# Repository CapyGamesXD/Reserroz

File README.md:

# Reserroz

This is a less expensive alternative to the official Flipper Zero Wi-Fi Devboard. 

It is capable of running GhostESP and Wi-Fi Marauder*

The total cost for 2 units (shipping included) came out to <£30 each from JLCPCB - £5 less than the devboard. If they were manufactured manually, they would be significantly cheaper than the official version. It features an ESP32 S3 Mini 1 (double the cores than the official one, with Bluetooth!) as the main microcontroller chip. 

*As of now, neither has been tested as the device has not yet been manufactured.

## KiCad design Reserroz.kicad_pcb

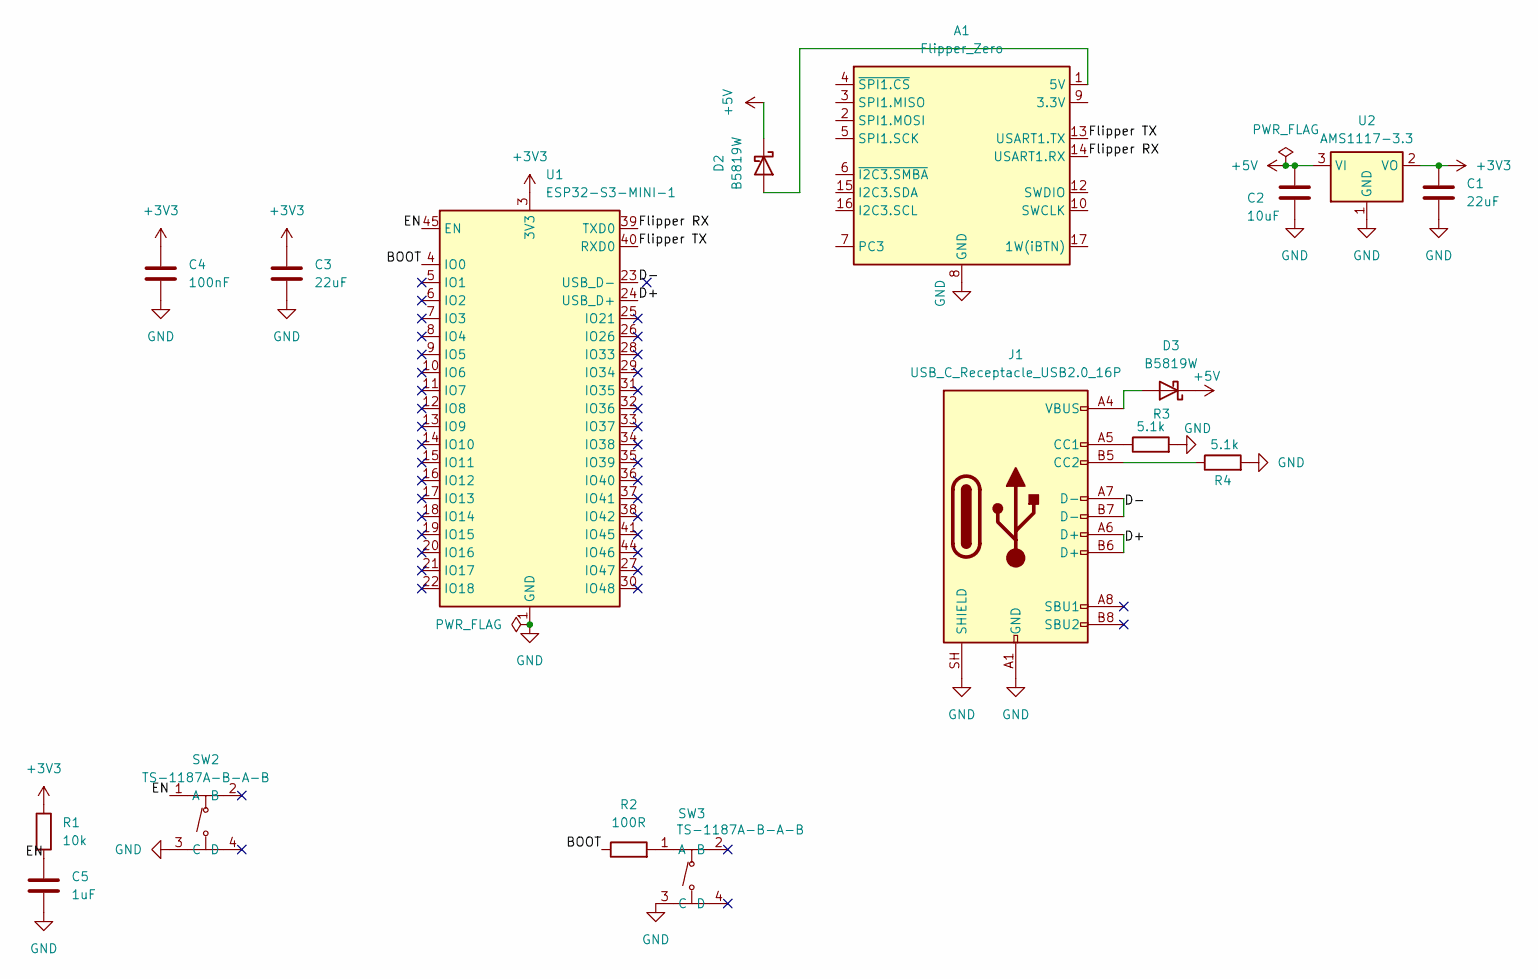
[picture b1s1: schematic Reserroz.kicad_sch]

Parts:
A1: Flipper_Zero; Flipper_Zero_Angled
C1, C3: 22uF; C_1210_3225Metric; LCSC C16196568
C2: 10uF; C_1210_3225Metric; LCSC C55072786
C4: 100nF; C_0603_1608Metric; LCSC C14663
C5: 1uF; C_0603_1608Metric; LCSC C14663
D2, D3: B5819W; D_SOD-123; LCSC C8598
J1: USB_C_Receptacle_USB2.0_16P; USB_C_Receptacle_GCT_USB4105-xx-A_16P_TopMnt_Horizontal
R1: 10k; R_0805_2012Metric
R2: 100R; R_0805_2012Metric; LCSC C2907218
R3, R4: 5.1k; R_0805_2012Metric
SW2, SW3: TS-1187A-B-A-B; SW-SMD_4P-L5.1-W5.1-P3.70-LS6.5-TL_H1.5; MPN TS-1187A-B-A-B; LCSC Part C318884
U1: ESP32-S3-MINI-1; ESP32-S2-MINI-1
U2: AMS1117-3.3; SOT-223-3_TabPin2

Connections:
+3V3: C1.1, C3.1, C4.1, R1.1, U1.3 (3V3), U2.2 (VO); also elsewhere on the board
+5V: C2.1, D2.1 (K), D3.1 (K), U2.3 (VI)
/BOOT: R2.1, U1.4 (IO0)
/D+: J1.A6 (D+), J1.B6 (D+), U1.24 (USB_D+)
/D-: J1.A7 (D-), J1.B7 (D-), U1.23 (USB_D-)
/EN: C5.1, R1.2, SW2.1 (A), U1.45 (EN)
/F5V: A1.1 (5V), D2.2 (A); also elsewhere on the board
/FSCL: A1.16 (I2C3.SCL); also elsewhere on the board
/FSDA: A1.15 (I2C3.SDA); also elsewhere on the board
/Flipper 3V3: A1.9 (3.3V); also elsewhere on the board
/Flipper RX: A1.14 (USART1.RX), U1.39 (TXD0)
/Flipper TX: A1.13 (USART1.TX), U1.40 (RXD0)
GND: A1.8 (GND), A1.11 (GND), A1.18 (GND), C1.2, C2.2, C3.2, C4.2, C5.2, J1.A1 (GND), J1.A12 (GND), J1.B1 (GND), J1.B12 (GND), J1.SH (SHIELD), R3.2, R4.2, SW2.3 (C), SW3.3 (C), U1.1 (GND), U1.2 (GND), U1.42 (GND), U1.43 (GND), U1.46 (GND), U1.47 (GND), U1.48 (GND), U1.49 (GND), U1.50 (GND), U1.51 (GND), U1.52 (GND), U1.53 (GND), U1.54 (GND), U1.55 (GND), U1.56 (GND), U1.57 (GND), U1.58 (GND), U1.59 (GND), U1.60 (GND), U1.61 (GND), U1.62 (GND), U1.63 (GND), U1.64 (GND), U1.65 (GND), U2.1 (GND); also elsewhere on the board
unnamed: D3.2 (A), J1.A4 (VBUS), J1.A9 (VBUS), J1.B4 (VBUS), J1.B9 (VBUS)
unnamed: J1.A5 (CC1), R3.1
unnamed: J1.B5 (CC2), R4.1
unnamed: R2.2, SW3.1 (A)

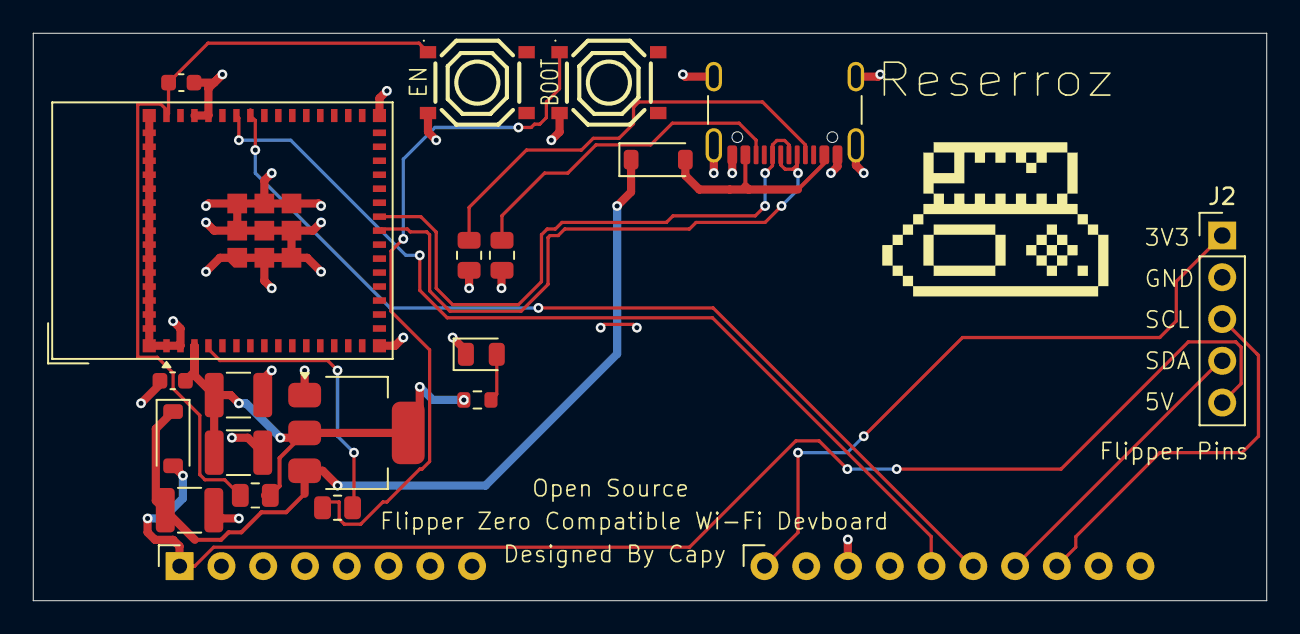
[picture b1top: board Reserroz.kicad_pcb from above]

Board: 2 copper layers, 75.0 x 34.5 mm, 20 parts (0 on the bottom side), 18 nets.

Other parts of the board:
D1: LED; LED_0805_2012Metric
J2: Conn_01x05_Pin; PinHeader_1x05_P2.54mm_Vertical
R5: 1k; R_0603_1608Metric

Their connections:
+3V3: R5.2; also elsewhere on the board
/F5V: J2.5; also elsewhere on the board
/FSCL: J2.3; also elsewhere on the board
/FSDA: J2.4; also elsewhere on the board
/Flipper 3V3: J2.1; also elsewhere on the board
GND: D1.1 (K), J2.2; also elsewhere on the board
unnamed: D1.2 (A), R5.1

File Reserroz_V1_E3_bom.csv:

Designator,Footprint,Quantity,Value,LCSC Part #
"C1, C3",1210,2,22uF,C16196568
C2,1210,1,10uF,C55072786
C4,0603,1,100nF,C14663
C5,0603,1,1uF,C14663
D1,0805,1,LED,C19171390
"D2, D3",D_SOD-123,2,B5819W,C8598
J1,USB_C_Receptacle_GCT_USB4105-xx-A_16P_TopMnt_Horizontal,1,USB_C_Receptacle_USB2.0_16P,C3020560
R1,0805,1,10k,
R2,0805,1,100R,C2907218
"R3, R4",0805,2,5.1k,
R5,0603,1,1k,C19706564
"SW2, SW3",SW-SMD_4P-L5.1-W5.1-P3.70-LS6.5-TL_H1.5,2,TS-1187A-B-A-B,C318884
U1,ESP32-S2-MINI-1,1,ESP32-S3-MINI-1,
U2,SOT-223-3_TabPin2,1,AMS1117-3.3,
